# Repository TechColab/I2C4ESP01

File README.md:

# I2C4ESP01
Carrier board for all components needed for a simple I2C on ESP-01 project.  

Designed to fit a 1590A aluminium box with a cut-out for 0.96" OLED display - just under 20x40mm  
Yes, the WiFi still works!  
Yes, there's enough space for the Qwiic connector wires under the ESP-01.  

Flexible, milti-purpose design with essential and common components, power-bus and a mini-patch bay for intermediary components. 
E.g. pull-ups, resistor-dividers, R-C filters etc.  
Accept ESP-01S and ESP-01 with pads to use RST and CHPS or tie them to 3v3 by JP2.  
JP1 allows option to dump power capacitor to GND upon unplugging the DC barel jack.  

## Changes from Rev 0.2 to Rev 0.3
Fixed missing GND connection for Qwiic connector.

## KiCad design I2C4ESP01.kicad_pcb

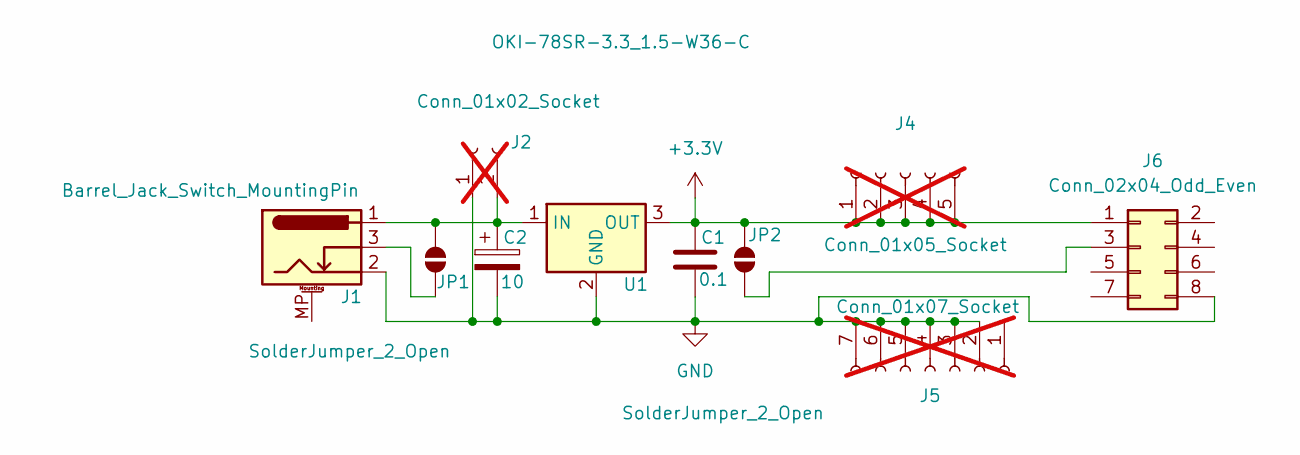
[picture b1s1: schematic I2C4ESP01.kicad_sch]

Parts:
C1: 0.1; C_Disc_D4.7mm_W2.5mm_P5.00mm
C2: 10; CP_Radial_D4.0mm_P1.50mm
J1: Barrel_Jack_Switch_MountingPin; BarrelJack_Wuerth_6941xx301002
J2: Conn_01x02_Socket; PinSocket_1x02_P2.54mm_Vertical; not fitted
J4: Conn_01x05_Socket; PinSocket_1x05_P2.54mm_Vertical; not fitted
J5: Conn_01x07_Socket; PinSocket_1x07_P2.54mm_Vertical; not fitted
J6: Conn_02x04_Odd_Even; IDC-Header_2x04_P2.54mm_Vertical
JP1, JP2: SolderJumper_2_Open; SolderJumper-2_P1.3mm_Open_Pad1.0x1.5mm
U1: OKI-78SR-3.3_1.5-W36-C; Converter_DCDC_Murata_OKI-78SR_Vertical

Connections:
+3.3V: C1.1, J4.1, J4.2, J4.3, J4.4, J4.5, J6.1, JP2.2 (B), U1.3 (OUT)
GND: C1.2, C2.2, J1.2, J2.1, J5.2, J5.3, J5.4, J5.5, J5.6, J5.7, J6.8, U1.2 (GND)
unnamed: C2.1, J1.1, J2.2, JP1.2 (B), U1.1 (IN)
unnamed: J6.3, JP2.1 (A)
unnamed: J1.3, JP1.1 (A)

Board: 2 copper layers, 11 parts (3 on the bottom side), 5 nets, no tracks yet.

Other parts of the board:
J3: JST_PH_B4B-PH-K_1x04_P2.00mm_Vertical
